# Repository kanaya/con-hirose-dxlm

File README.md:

# con-hirose-dxlm

[ヒロセ電機製デジタル放送機器対応D端子コネクタ](https://www.hirose.com/product/jp/download_file/key_name/DX%2ALM/category/Catalog/doc_file_id/49665/?file_category_id=4&item_id=129&is_series=1)のEagleライブラリです．

D端子コネクタから14ピンMLコネクタへの変換アダプタ基板を2種類用意しました．

* extra/hardware/dx10lm1-14se-to-ml-14p -- D端子-MLコネクタ変換基板（ストレート）
* extra/hardware/dx10lm1-14se-to-ml-14p-cross -- D端子-MLコネクタ変換基盤（クロス）

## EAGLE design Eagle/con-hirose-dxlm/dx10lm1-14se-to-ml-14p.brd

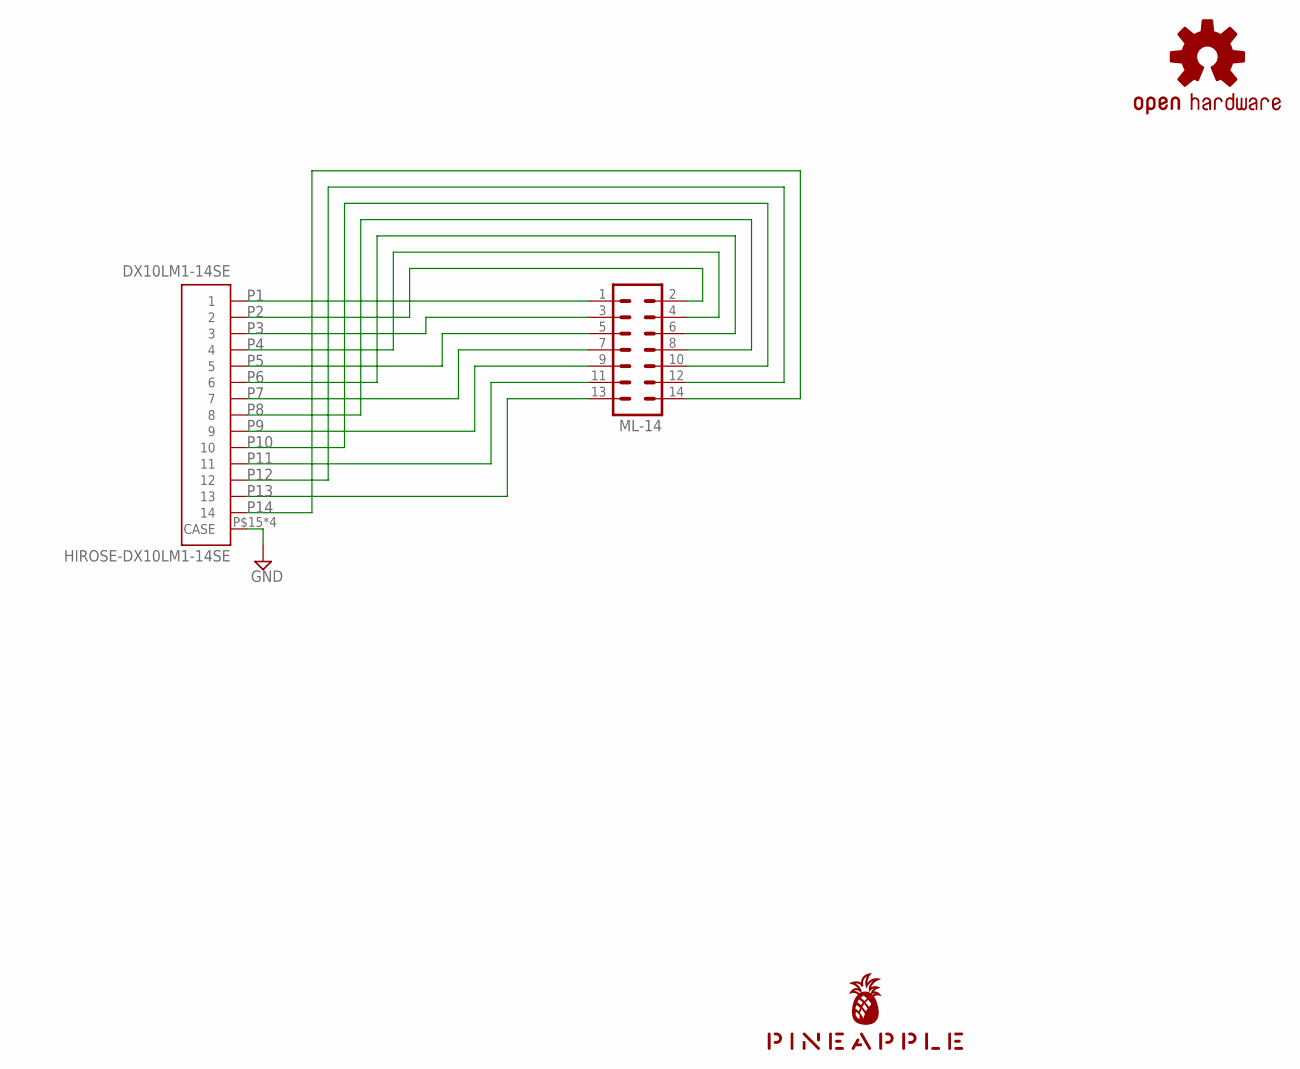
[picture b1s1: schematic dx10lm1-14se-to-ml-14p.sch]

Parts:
DX10LM1-14SE: HIROSE-DX10LM1-14SE
LOGO1: OSHW-LOGOS-COPPER; OSHW-LOGO-S_COPPER
ML-14: ML14L
U$1: PINEAPPLE450_SILK

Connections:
GND: DX10LM1-14SE.P$15 (CASE), DX10LM1-14SE.P$16 (CASE), DX10LM1-14SE.P$17 (CASE), DX10LM1-14SE.P$18 (CASE)
P1: DX10LM1-14SE.P$1 (1), ML-14.1
P2: DX10LM1-14SE.P$2 (2), ML-14.2
P3: DX10LM1-14SE.P$3 (3), ML-14.3
P4: DX10LM1-14SE.P$4 (4), ML-14.4
P5: DX10LM1-14SE.P$5 (5), ML-14.5
P6: DX10LM1-14SE.P$6 (6), ML-14.6
P7: DX10LM1-14SE.P$7 (7), ML-14.7
P8: DX10LM1-14SE.P$8 (8), ML-14.8
P9: DX10LM1-14SE.P$9 (9), ML-14.9
P10: DX10LM1-14SE.P$10 (10), ML-14.10
P11: DX10LM1-14SE.P$11 (11), ML-14.11
P12: DX10LM1-14SE.P$12 (12), ML-14.12
P13: DX10LM1-14SE.P$13 (13), ML-14.13
P14: DX10LM1-14SE.P$14 (14), ML-14.14

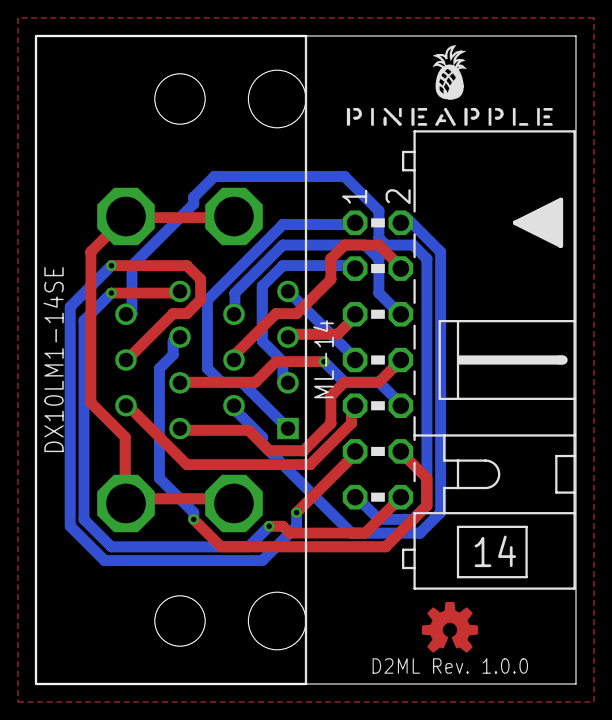
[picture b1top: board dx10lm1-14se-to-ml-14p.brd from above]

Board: 2 copper layers, 30.0 x 36.0 mm, 4 parts (0 on the bottom side), 15 nets.

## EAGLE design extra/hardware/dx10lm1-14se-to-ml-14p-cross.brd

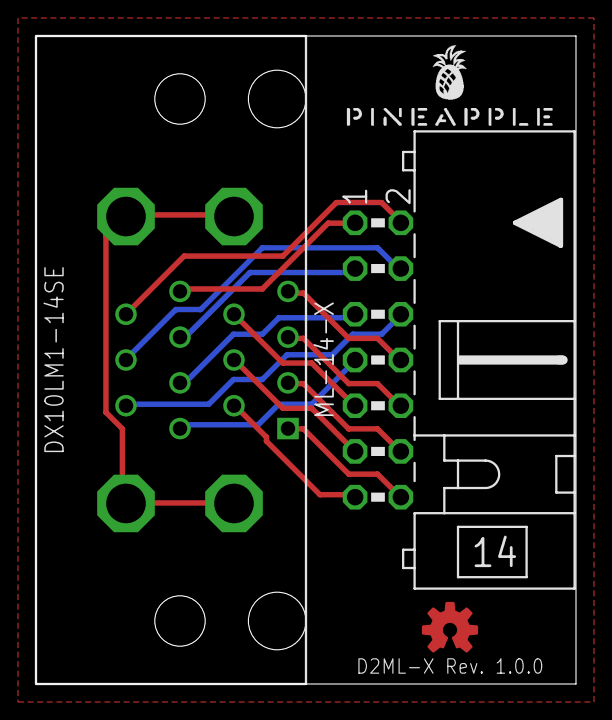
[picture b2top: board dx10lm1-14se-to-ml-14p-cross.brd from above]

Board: 2 copper layers, 30.0 x 36.0 mm, 4 parts (0 on the bottom side), 15 nets.

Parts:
DX10LM1-14SE: HIROSE-DX10LM1-14SE
LOGO1: OSHW-LOGOS-COPPER; OSHW-LOGO-S_COPPER
ML-14-X: ML14L
U$1: PINEAPPLE450_SILK

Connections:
GND: DX10LM1-14SE.P$15, DX10LM1-14SE.P$16, DX10LM1-14SE.P$17, DX10LM1-14SE.P$18
P1: DX10LM1-14SE.P$1, ML-14-X.14
P2: DX10LM1-14SE.P$2, ML-14-X.13
P3: DX10LM1-14SE.P$3, ML-14-X.12
P4: DX10LM1-14SE.P$4, ML-14-X.11
P5: DX10LM1-14SE.P$5, ML-14-X.10
P6: DX10LM1-14SE.P$6, ML-14-X.9
P7: DX10LM1-14SE.P$7, ML-14-X.8
P8: DX10LM1-14SE.P$8, ML-14-X.7
P9: DX10LM1-14SE.P$9, ML-14-X.6
P10: DX10LM1-14SE.P$10, ML-14-X.5
P11: DX10LM1-14SE.P$11, ML-14-X.4
P12: DX10LM1-14SE.P$12, ML-14-X.3
P13: DX10LM1-14SE.P$13, ML-14-X.2
P14: DX10LM1-14SE.P$14, ML-14-X.1

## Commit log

2015-04-07 Hirose DX10LM-14SE.
2015-04-15 Bug fix.
2015-04-18 Created DX10LM1-14SE pattern from scratch.
2015-04-18 Removed old files.
2018-03-12 GND pins.
2018-08-06 .gitignore.
2018-08-06 Fixed soldering pattern.
2018-08-06 Fixed description.
2018-09-11 Added experimental DX10LM1-14SE to ML 14p adapter.
2018-09-13 Renewed D2ML adaptor.
2018-09-16 Added "Cross" version of DX10LM1-14SE to ML 14p adaptor.
2018-09-16 Moved extra files to extra dir.
2018-09-16 Updated README.

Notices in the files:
parts and their libraries:
SparkFun-Aesthetics: Licensing: Creative Commons ShareAlike 4.0 International - https://creativecommons.org/licenses/by-sa/4.0
